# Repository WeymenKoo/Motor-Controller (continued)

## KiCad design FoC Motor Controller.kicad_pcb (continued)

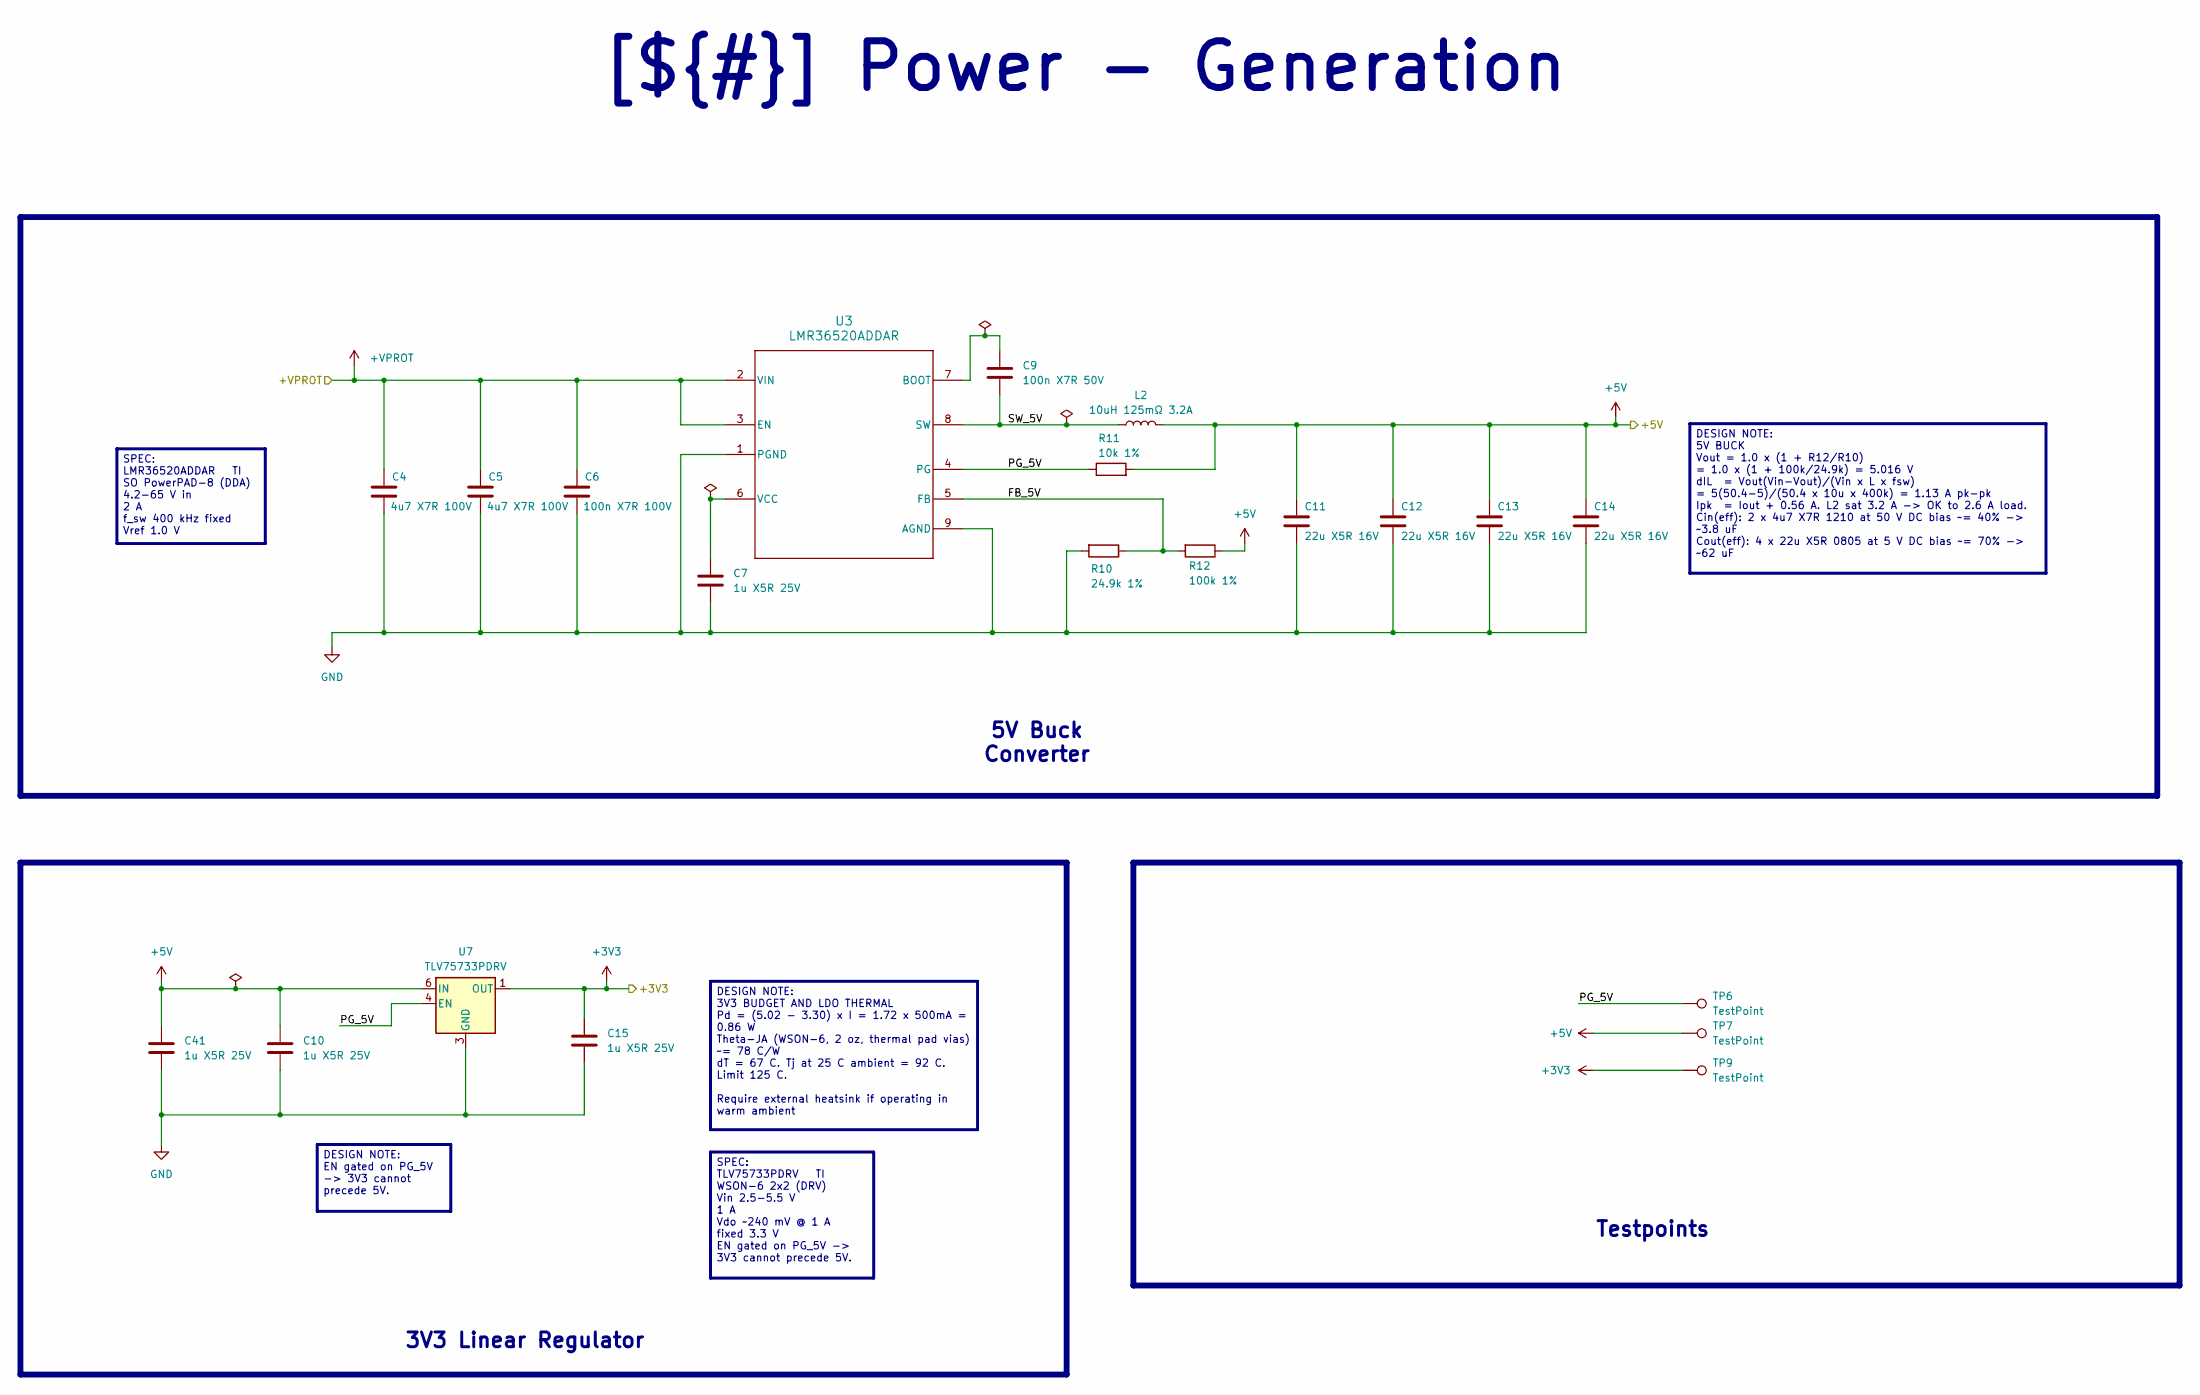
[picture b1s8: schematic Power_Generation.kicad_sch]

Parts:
C4, C5: 4u7 X7R 100V; C_1210_3225Metric_Pad1.33x2.70mm_HandSolder
C6: 100n X7R 100V; C_0603_1608Metric_Pad1.08x0.95mm_HandSolder
C7, C10, C15, C41: 1u X5R 25V; C_0603_1608Metric
C9: 100n X7R 50V; C_0402_1005Metric
C11, C12, C13, C14: 22u X5R 16V; C_0805_2012Metric
L2: 10uH 125mΩ 3.2A; L_Changjiang_FXL0530
R10: 24.9k 1%; R_0402_1005Metric
R11: 10k 1%; R_0402_1005Metric
R12: 100k 1%; R_0402_1005Metric
TP6, TP7, TP9: TestPoint; TestPoint-0.5mm
U3: LMR36520ADDAR; DDA0008J
U7: TLV75733PDRV; WDFN-6_2x2mm

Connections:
+3V3: C15.1, TP9.1 (1_1), U7.1 (OUT); also elsewhere on the board
+5V: C10.1, C11.1, C12.1, C13.1, C14.1, C41.1, L2.2, R11.2, R12.1, TP7.1 (1_1), U7.6 (IN); also elsewhere on the board
+VPROT: C4.1, C5.1, C6.1, U3.2 (VIN), U3.3 (EN); also elsewhere on the board
/Project Architecture/Power - Generation/FB_5V: R10.1, R12.2, U3.5 (FB)
/Project Architecture/Power - Generation/PG_5V: R11.1, TP6.1 (1_1), U3.4 (PG), U7.4 (EN)
/Project Architecture/Power - Generation/SW_5V: C9.2, L2.1, U3.8 (SW)
GND: C4.2, C5.2, C6.2, C7.2, C10.2, C11.2, C12.2, C13.2, C14.2, C15.2, C41.2, R10.2, U3.1 (PGND), U3.9 (AGND), U7.3 (GND), U7.7 (GND); also elsewhere on the board
unnamed: C9.1, U3.7 (BOOT)
unnamed: C7.1, U3.6 (VCC)

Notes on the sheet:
3V3 Linear Regulator
Testpoints
SPEC: TLV75733PDRV TI WSON-6 2x2 (DRV) Vin 2.5-5.5 V 1 A Vdo ~240 mV @ 1 A fixed 3.3 V EN gated on PG_5V -> 3V3 cannot precede 5V.
DESIGN NOTE: EN gated on PG_5V -> 3V3 cannot precede 5V.
DESIGN NOTE: 5V BUCK Vout = 1.0 x (1 + R12/R10) = 1.0 x (1 + 100k/24.9k) = 5.016 V dIL = Vout(Vin-Vout)/(Vin x L x fsw) = 5(50.4-5)/(50.4 x 10u x 400k) = 1.13 A pk-pk Ipk = Iout + 0.56 A. L2 sat 3.2 A -> OK to 2.6 A load. Cin(eff): 2 x 4u7 X7R 1210 at 50 V DC bias ~= 40% -> ~3.8 uF Cout(eff): 4 x 2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
DESIGN NOTE: 3V3 BUDGET AND LDO THERMAL Pd = (5.02 - 3.30) x I = 1.72 x 500mA = 0.86 W Theta-JA (WSON-6, 2 oz, thermal pad vias) ~= 78 C/W dT = 67 C. Tj at 25 C ambient = 92 C. Limit 125 C. Require external heatsink if operating in warm ambient
5V Buck Converter
[${#}] Power - Generation
SPEC: LMR36520ADDAR TI SO PowerPAD-8 (DDA) 4.2-65 V in 2 A f_sw 400 kHz fixed Vref 1.0 V

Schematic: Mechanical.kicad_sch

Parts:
C73, C74, C75, C76: 1n X7R 1kV; C_0603_1608Metric_Pad1.08x0.95mm_HandSolder
H4, H5, H6, H7: M3_MountingHole_Pad; MountingHole_3.2mm_M3_Pad_Via
R56, R57, R59: 0R 1% 1/8W; R_0805_2012Metric; not fitted
R58: 0R 1% 1/8W; R_0805_2012Metric

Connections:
CHASSIS1: C73.1, H4.1 (1_1), R56.1
CHASSIS2: C74.1, H5.1 (1_1), R57.1
CHASSIS3: C75.1, H6.1 (1_1), R58.1; also elsewhere on the board
CHASSIS4: C76.1, H7.1 (1_1), R59.1
GND: C73.2, C74.2, C75.2, C76.2, R56.2, R57.2, R58.2, R59.2; also elsewhere on the board

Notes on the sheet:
[${#}] Mechanical - Mounting Holes
DESIGN NOTE: 0-Ohmresistor provides low-impedance bond between chassis and signal GND. Be aware of ground loops through cable shield.
DESIGN NOTE: Optional RC filter for chassis grounding. Capacitors offer multi-point low-impedance connections at high-frequencies.

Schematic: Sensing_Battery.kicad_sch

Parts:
C60: 100n X7R 50V; C_0402_1005Metric
R36: 2k 1%; R_0402_1005Metric
R72: 24.9k 1%; R_0402_1005Metric
R73: 12.4k 1%; R_0402_1005Metric

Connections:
+VPROT: R72.1; also elsewhere on the board
/Project Architecture/MCU - IOs/VBAT_SENSE: C60.1, R36.1, R73.2; also elsewhere on the board
GND: C60.2, R36.2; also elsewhere on the board
unnamed: R72.2, R73.1

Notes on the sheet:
Battery Voltage Sensor
[${#}] Sensing - Battery
DESIGN NOTE: Ratio = R36/(R72+R73+R36) = 2/(24.9+12.4+2) = 2/39.3 = 0.05089 at 50.4 V -> 2.565 V at 56.0 V -> 2.850 V clips at VREF+ = 3.3 V when Vbus = 64.8 V Divider current at 50.4 V = 1.283 mA (continuous pack drain) P(R72) = 41 mW, P(R73) = 20 mW Rth = (R72+R73) || R36 = 1.90 k tau = 190 us, f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

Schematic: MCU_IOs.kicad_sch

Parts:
C16: 22u X5R 16V; C_0805_2012Metric
C17, C20, C24: 1u X5R 25V; C_0603_1608Metric
C18, C19, C21, C22, C23: 100n X7R 50V; C_0402_1005Metric
C25, C26, C27: 2n2 X7R 50V; C_0402_1005Metric
C28, C29: 12pF 50V C0G; C_0402_1005Metric
R13, R14, R15: 56R 1%; R_0402_1005Metric
TP11, TP12, TP13, TP14, TP15, TP16, TP17, TP18, TP19, TP20, TP21, TP22, TP23, TP24, TP25, TP26, TP27, TP28, TP29, TP30, TP31, TP32, TP33, TP34, TP35, TP36: TestPoint; TestPoint-0.5mm
U5: STM32G431RBTx; LQFP-64_10x10mm_P0.5mm
X1: SMD3225-4; Crystal_SMD_3225-4Pin_3.2x2.5mm

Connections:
+3V3: C16.1, C17.1, C18.1, C19.1, C20.1, C21.1, C22.1, C23.1, C24.1, U5.1 (VBAT), U5.16 (VDD), U5.28 (VREF+), U5.29 (VDDA), U5.32 (VDD), U5.48 (VDD), U5.64 (VDD); also elsewhere on the board
/Project Architecture/Interface - CAN FD/FDCAN_RX: TP12.1 (1_1), U5.61 (PB8); also elsewhere on the board
/Project Architecture/Interface - CAN FD/FDCAN_TX: TP11.1 (1_1), U5.62 (PB9); also elsewhere on the board
/Project Architecture/Interface - Interconnects/I2C3_SCL: U5.40 (PC8); also elsewhere on the board
/Project Architecture/Interface - Interconnects/I2C3_SDA: U5.41 (PC9); also elsewhere on the board
/Project Architecture/Interface - Interconnects/NRST: U5.7 (PG10); also elsewhere on the board
/Project Architecture/Interface - Interconnects/POS_SENSOR_CLK: U5.19 (PA5); also elsewhere on the board
/Project Architecture/Interface - Interconnects/POS_SENSOR_CS: U5.18 (PA4); also elsewhere on the board
/Project Architecture/Interface - Interconnects/POS_SENSOR_CS2: U5.22 (PC4); also elsewhere on the board
/Project Architecture/Interface - Interconnects/POS_SENSOR_MISO: U5.20 (PA6); also elsewhere on the board
/Project Architecture/Interface - Interconnects/POS_SENSOR_MOSI: U5.21 (PA7); also elsewhere on the board
/Project Architecture/Interface - Interconnects/SWCLK: U5.50 (PA14); also elsewhere on the board
/Project Architecture/Interface - Interconnects/SWDIO: U5.49 (PA13); also elsewhere on the board
/Project Architecture/Interface - Interconnects/UART1_RX: TP14.1 (1_1), U5.59 (PB6); also elsewhere on the board
/Project Architecture/Interface - Interconnects/UART1_TX: TP13.1 (1_1), U5.60 (PB7); also elsewhere on the board
/Project Architecture/MCU - IOs/DRV_CAL: TP29.1 (1_1), U5.38 (PC6); also elsewhere on the board
/Project Architecture/MCU - IOs/DRV_CS: TP33.1 (1_1), U5.55 (PD2); also elsewhere on the board
/Project Architecture/MCU - IOs/DRV_ENABLE: TP28.1 (1_1), U5.39 (PC7); also elsewhere on the board
/Project Architecture/MCU - IOs/DRV_MISO: TP30.1 (1_1), U5.53 (PC11); also elsewhere on the board
/Project Architecture/MCU - IOs/DRV_MOSI: TP31.1 (1_1), U5.54 (PC12); also elsewhere on the board
/Project Architecture/MCU - IOs/DRV_SCLK: TP32.1 (1_1), U5.52 (PC10); also elsewhere on the board
/Project Architecture/MCU - IOs/DRV_nFAULT: TP27.1 (1_1), U5.51 (PA15); also elsewhere on the board
/Project Architecture/MCU - IOs/FILTER_SOA: C27.1, R15.1, TP17.1 (1_1), U5.33 (PB11)
/Project Architecture/MCU - IOs/FILTER_SOB: C26.1, R14.1, TP16.1 (1_1), U5.34 (PB12)
/Project Architecture/MCU - IOs/FILTER_SOC: C25.1, R13.1, TP15.1 (1_1), U5.36 (PB14)
/Project Architecture/MCU - IOs/MCU_LED: U5.58 (PB5); also elsewhere on the board
/Project Architecture/MCU - IOs/MOT_TEMP_SENSE: TP36.1 (1_1), U5.26 (PB2); also elsewhere on the board
/Project Architecture/MCU - IOs/OSC_IN: C29.1, U5.5 (PF0), X1.1
/Project Architecture/MCU - IOs/OSC_OUT: C28.1, U5.6 (PF1), X1.3
/Project Architecture/MCU - IOs/PA0: U5.12 (PA0)
/Project Architecture/MCU - IOs/PA1: U5.13 (PA1)
/Project Architecture/MCU - IOs/PA2: U5.14 (PA2)
/Project Architecture/MCU - IOs/PA3: U5.17 (PA3)
/Project Architecture/MCU - IOs/PB3: U5.56 (PB3)
/Project Architecture/MCU - IOs/PB10: U5.30 (PB10)
/Project Architecture/MCU - IOs/PB13: U5.35 (PB13)
/Project Architecture/MCU - IOs/PC0: U5.8 (PC0)
/Project Architecture/MCU - IOs/PC1: U5.9 (PC1)
/Project Architecture/MCU - IOs/PC2: U5.10 (PC2)
/Project Architecture/MCU - IOs/PC3: U5.11 (PC3); also elsewhere on the board
/Project Architecture/MCU - IOs/PC5: U5.23 (PC5)
/Project Architecture/MCU - IOs/PC13: U5.2 (PC13)
/Project Architecture/MCU - IOs/PC14: U5.3 (PC14)
/Project Architecture/MCU - IOs/PC15: U5.4 (PC15)
/Project Architecture/MCU - IOs/PWM_PHASEA_H: TP21.1 (1_1), U5.42 (PA8); also elsewhere on the board
/Project Architecture/MCU - IOs/PWM_PHASEA_L: TP22.1 (1_1), U5.45 (PA11); also elsewhere on the board
/Project Architecture/MCU - IOs/PWM_PHASEB_H: TP23.1 (1_1), U5.43 (PA9); also elsewhere on the board
/Project Architecture/MCU - IOs/PWM_PHASEB_L: TP24.1 (1_1), U5.46 (PA12); also elsewhere on the board
/Project Architecture/MCU - IOs/PWM_PHASEC_H: TP25.1 (1_1), U5.44 (PA10); also elsewhere on the board
/Project Architecture/MCU - IOs/PWM_PHASEC_L: TP26.1 (1_1), U5.37 (PB15); also elsewhere on the board
/Project Architecture/MCU - IOs/PWR_LED: U5.57 (PB4); also elsewhere on the board
/Project Architecture/MCU - IOs/SOA: R15.2, TP20.1 (1_1); also elsewhere on the board
/Project Architecture/MCU - IOs/SOB: R14.2, TP19.1 (1_1); also elsewhere on the board
/Project Architecture/MCU - IOs/SOC: R13.2, TP18.1 (1_1); also elsewhere on the board
/Project Architecture/MCU - IOs/TEMP_SENSE: TP35.1 (1_1), U5.25 (PB1); also elsewhere on the board
/Project Architecture/MCU - IOs/VBAT_SENSE: TP34.1 (1_1), U5.24 (PB0); also elsewhere on the board
GND: C16.2, C17.2, C18.2, C19.2, C20.2, C21.2, C22.2, C23.2, C24.2, C25.2, C26.2, C27.2, C28.2, C29.2, U5.15 (VSS), U5.27 (VSSA), U5.31 (VSS), U5.47 (VSS), U5.63 (VSS), X1.2, X1.4; also elsewhere on the board

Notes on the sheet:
SWD
DESIGN NOTE: CALC - CRYSTAL LOAD CL = (C28 x C29)/(C28 + C29) + Cstray = (12 x 12)/24 + ~5 = 11 pF Selected a crystal specified for CL = 11-12 pF.
Analog IO
REVIEW
[${#}] MCU - IOs
SPEC: ADC CHANNEL MAP FILTER_SOA PB11 ADC1_IN14 / ADC2_IN14 (both) FILTER_SOB PB12 ADC1_IN11 (ADC1 only) FILTER_SOC PB14 ADC1_IN5 (ADC1 only) VBAT_SENSE PB0 ADC1_IN15 TEMP_SENSE PB1 ADC1_IN12 MOT_TEMP PB2 ADC2_IN12 Simultaneous dual-ADC sampling MUST pair SOA (on ADC2) with SOB or SOC (on ADC1). Ph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
MCU - STM32G431RBT6
FIRMWARE - MANDATORY AT BOOT 1. Program nSWBOOT0 = 0 so BOOT0 comes from the option bit, not PB8 (PB8 = FDCAN1_RX). 2. Set PWR_CR3.UCPD1_DBDIS = 1 BEFORE enabling TIM1. PA9/PA10 (PWM_PHASEB_H / PWM_PHASEC_H) are UCPD1_DBCC1/2. A high level enables internal 5.1k pull-downs on PB6 (UART TX) and PB4 (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
Testpoints
Digital IO

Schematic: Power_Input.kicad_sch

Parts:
D1: SMCJ51CA; D_SMC_TVS
H8, H9: Power; MountingHole_3.2mm_M3_Pad_Via

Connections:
+VPROT: D1.2 (A), H8.1 (1_1); also elsewhere on the board
GND: D1.1 (K), H9.1 (1_1); also elsewhere on the board

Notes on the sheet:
ACCEPTED RISK: D1 clamps at 82.4 V. Downstream absolute maximums: DRV8323 VM/VDRAIN 65 V LMR36520 VIN 65 V TLV75733 VIN 5.5 V (fed from +5V, not exposed) D1 therefore does NOT protect the board against an event large enough to engage it. SOLUTION: Upstream PDB handles protection
ASSEMBLY: D3.2mm solder pad, no connector
SPEC: SMCJ51CA Littelfuse SMC / DO-214AB Vrwm 51 V Vbr(min) 56.7 V Vclamp 82.4 V @ 18.2 A 1500 W Bidirectional (CA suffix)
Input Power
[${#}] Power - Input

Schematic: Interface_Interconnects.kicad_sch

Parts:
C42: 2n2 X7R 50V; C_0402_1005Metric
C67, C70, C72, C78, C81: 100n X7R 50V; C_0402_1005Metric
C68: 47n X7R 100V; C_0603_1608Metric_Pad1.08x0.95mm_HandSolder
D4, D7: PESD2CANFD24V-K; TVS_PESD2CANFD24V-UX; PARTREV V.4
J1, J3, J4, J5: Conn_01x04_MountingPin; JST_GH_BM04B-GHS-TBT_1x04-1MP_P1.25mm_Vertical
J2: Conn_01x03; 1x03_P2.54mm; not fitted
J6: Conn_01x07_MountingPin; JST_GH_BM07B-GHS-TBT_1x07-1MP_P1.25mm_Vertical
J7: Conn_01x05; PinHeader_1x05_P2.54mm_Vertical
J10, J11: Conn_01x02_MountingPin; JST_GH_BM02B-GHS-TBT_1x02-1MP_P1.25mm_Vertical
R41: 1k 1%; R_0402_1005Metric
R42, R44: 2k 1%; R_0402_1005Metric
R45, R46: 60R4 1%; R_0805_2012Metric
R47, R48, R49, R50, R51, R52, R53, R54: 100R 1%; R_0402_1005Metric
SW1: SW_Push_DPDT; Slide_DPDT_SMD_7.2x3.5mm

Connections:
+3V3: C72.1, C78.1, C81.1, J1.2, J3.2, J6.2, J7.1, R42.1, R44.1; also elsewhere on the board
+5V: C70.1, J6.1; also elsewhere on the board
/Project Architecture/Interface - CAN FD/FDCAN_N: D4.2, D7.2, J2.1, J4.2, J5.2, SW1.4 (A); also elsewhere on the board
/Project Architecture/Interface - CAN FD/FDCAN_P: D4.1, D7.1, J2.2, J4.3, J5.3, SW1.1 (A); also elsewhere on the board
/Project Architecture/Interface - Interconnects/AUX2_A: J6.4, R47.1
/Project Architecture/Interface - Interconnects/AUX2_B: J6.5, R49.1
/Project Architecture/Interface - Interconnects/AUX2_C: J6.6, R51.1
/Project Architecture/Interface - Interconnects/AUX2_D: J6.7, R53.1
/Project Architecture/Interface - Interconnects/FDCAN_TERM_B: R46.2, SW1.5 (B)
/Project Architecture/Interface - Interconnects/FDCAN_TERM_MID: C68.1, R45.2, R46.1
/Project Architecture/Interface - Interconnects/FDCAN_TERM_T: R45.1, SW1.2 (B)
/Project Architecture/Interface - Interconnects/I2C3_SCL: R44.2, R50.2; also elsewhere on the board
/Project Architecture/Interface - Interconnects/I2C3_SDA: R42.2, R48.2; also elsewhere on the board
/Project Architecture/Interface - Interconnects/MOT_NTC_H: J10.1; also elsewhere on the board
/Project Architecture/Interface - Interconnects/MOT_NTC_L: J10.2; also elsewhere on the board
/Project Architecture/Interface - Interconnects/NRST: C67.1, J7.2; also elsewhere on the board
/Project Architecture/Interface - Interconnects/POS_SENSOR_CLK: R49.2; also elsewhere on the board
/Project Architecture/Interface - Interconnects/POS_SENSOR_CS2: R47.2; also elsewhere on the board
/Project Architecture/Interface - Interconnects/POS_SENSOR_MISO: R51.2; also elsewhere on the board
/Project Architecture/Interface - Interconnects/POS_SENSOR_MOSI: R53.2; also elsewhere on the board
/Project Architecture/Interface - Interconnects/SWCLK: J7.3; also elsewhere on the board
/Project Architecture/Interface - Interconnects/SWDIO: J7.4; also elsewhere on the board
/Project Architecture/Interface - Interconnects/UART1_RX: R54.2; also elsewhere on the board
/Project Architecture/Interface - Interconnects/UART1_TX: R52.2; also elsewhere on the board
/Project Architecture/MCU - IOs/DRV_ENABLE: C42.1, J11.1, R41.1; also elsewhere on the board
/Project Architecture/MCU - IOs/PC3: R41.2; also elsewhere on the board
CHASSIS3: D4.3, D7.3; also elsewhere on the board
GND: C42.2, C67.2, C68.2, C70.2, C72.2, C78.2, C81.2, J1.1, J2.3, J3.1, J4.4, J5.4, J6.3, J7.5, J11.2; also elsewhere on the board
unnamed: J1.3, R52.1
unnamed: J1.4, R54.1
unnamed: J3.3, R48.1
unnamed: J3.4, R50.1

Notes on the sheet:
DESIGN NOTE: Loop closed = PC3 low = run; Loop open OR cable unplugged = PC3 high = hardware break.
DESIGN NOTE: J6 shares SPI1 (SCK/MISO/MOSI) with the on-board AS5047P (U1). Isolation is by chip select only: U1 on PA4, remote on PC4. AS5047P tri-states MISO when CSn is high (datasheet t_OZ), so two slaves on one bus is valid - but firmware MUST NOT assert both chip selects.
SWD (2.54mm Pin Header)
AUX2 Connector (Position Sensor SPI)
DESIGN NOTE: No ESD protection for prototype. Expected to be in lab environment.
Temperature
DESIGN NOTE: UART PIN NAMING Net UART1_TX lands on PB7 = USART1_RX. Net UART1_RX lands on PB6 = USART1_TX.
[${#}] Interface - Interconnects
FD_CAN Connectors and Termination

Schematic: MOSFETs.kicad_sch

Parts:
C34, C37, C39: 100uF 100V; CP_Radial_D10.0mm_P5.00mm; Voltage 1kV; Tolerance 100%
C35, C36, C45, C46, C56, C57: 2n2 X7R 100V; C_0805_2012Metric; not fitted
C38, C49, C58: 100n X7R 100V; C_0603_1608Metric_Pad1.08x0.95mm_HandSolder
C40, C43, C44, C47, C48, C50, C51, C52, C59: 4u7 X7R 100V; C_1210_3225Metric_Pad1.33x2.70mm_HandSolder
H1, H2, H3: Phase; MountingHole_3.2mm_M3_Pad_Via
NT1, NT2, NT3, NT4, NT5, NT6, NT7, NT8, NT9: NetTie_2; NetTie-2_SMD_Pad0.5mm
Q3, Q4, Q5, Q6, Q7, Q8: ISC030N10NM6; IFX-PG-TDSON-8-36-V
R20, R21, R25, R26, R30, R31: 0R 1% 1/8W; R_0805_2012Metric_Pad1.20x1.40mm_HandSolder
R22, R27, R32: 3mΩ 3W 1%; R_2512_6332Metric_Pad1.40x3.35mm_HandSolder
R23, R24, R28, R29, R33, R34: 3R9 1% 1/8W; R_0805_2012Metric_Pad1.20x1.40mm_HandSolder; not fitted

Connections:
+VPROT: C34.1, C37.1, C38.1, C39.1, C40.1, C43.1, C44.1, C47.1, C48.1, C49.1, C50.1, C51.1, C52.1, C58.1, C59.1, Q3.5 (DRAIN), Q3.6 (DRAIN), Q3.7 (DRAIN), Q3.8 (DRAIN), Q5.5 (DRAIN), Q5.6 (DRAIN), Q5.7 (DRAIN), Q5.8 (DRAIN), Q7.5 (DRAIN), Q7.6 (DRAIN), Q7.7 (DRAIN), Q7.8 (DRAIN), R23.1, R28.1, R33.1; also elsewhere on the board
/Project Architecture/Motor Control - Driver/GHA: R20.2; also elsewhere on the board
/Project Architecture/Motor Control - Driver/GHB: R25.2; also elsewhere on the board
/Project Architecture/Motor Control - Driver/GHC: R30.2; also elsewhere on the board
/Project Architecture/Motor Control - Driver/GLA: R21.2; also elsewhere on the board
/Project Architecture/Motor Control - Driver/GLB: R26.2; also elsewhere on the board
/Project Architecture/Motor Control - Driver/GLC: R31.2; also elsewhere on the board
/Project Architecture/Motor Control - Driver/MOSFETs/GH_A: Q3.4 (GATE), R20.1
/Project Architecture/Motor Control - Driver/MOSFETs/GH_B: Q5.4 (GATE), R25.1
/Project Architecture/Motor Control - Driver/MOSFETs/GH_C: Q7.4 (GATE), R30.1
/Project Architecture/Motor Control - Driver/MOSFETs/GL_A: Q4.4 (GATE), R21.1
/Project Architecture/Motor Control - Driver/MOSFETs/GL_B: Q6.4 (GATE), R26.1
/Project Architecture/Motor Control - Driver/MOSFETs/GL_C: Q8.4 (GATE), R31.1
/Project Architecture/Motor Control - Driver/MOSFETs/OUT_A: C35.2, C36.1, H1.1 (1_1), NT3.2, Q3.1 (SOURCE), Q3.2 (SOURCE), Q3.3 (SOURCE), Q4.5 (DRAIN), Q4.6 (DRAIN), Q4.7 (DRAIN), Q4.8 (DRAIN)
/Project Architecture/Motor Control - Driver/MOSFETs/OUT_B: C45.2, C46.1, H2.1 (1_1), NT6.2, Q5.1 (SOURCE), Q5.2 (SOURCE), Q5.3 (SOURCE), Q6.5 (DRAIN), Q6.6 (DRAIN), Q6.7 (DRAIN), Q6.8 (DRAIN)
/Project Architecture/Motor Control - Driver/MOSFETs/OUT_C: C56.2, C57.1, H3.1 (1_1), NT9.2, Q7.1 (SOURCE), Q7.2 (SOURCE), Q7.3 (SOURCE), Q8.5 (DRAIN), Q8.6 (DRAIN), Q8.7 (DRAIN), Q8.8 (DRAIN)
/Project Architecture/Motor Control - Driver/MOSFETs/RSHUNT_N_A: NT2.1; also elsewhere on the board
/Project Architecture/Motor Control - Driver/MOSFETs/RSHUNT_N_B: NT5.1; also elsewhere on the board
/Project Architecture/Motor Control - Driver/MOSFETs/RSHUNT_N_C: NT8.1; also elsewhere on the board
/Project Architecture/Motor Control - Driver/MOSFETs/RSHUNT_P_A: NT1.1; also elsewhere on the board
/Project Architecture/Motor Control - Driver/MOSFETs/RSHUNT_P_B: NT4.1; also elsewhere on the board
/Project Architecture/Motor Control - Driver/MOSFETs/RSHUNT_P_C: NT7.1; also elsewhere on the board
/Project Architecture/Motor Control - Driver/MOSFETs/SOURCE_A: C38.2, NT1.2, Q4.1 (SOURCE), Q4.2 (SOURCE), Q4.3 (SOURCE), R22.1, R24.2
/Project Architecture/Motor Control - Driver/MOSFETs/SOURCE_B: C49.2, NT4.2, Q6.1 (SOURCE), Q6.2 (SOURCE), Q6.3 (SOURCE), R27.1, R29.2
/Project Architecture/Motor Control - Driver/MOSFETs/SOURCE_C: C58.2, NT7.2, Q8.1 (SOURCE), Q8.2 (SOURCE), Q8.3 (SOURCE), R32.1, R34.2
/Project Architecture/Motor Control - Driver/SHA: NT3.1; also elsewhere on the board
/Project Architecture/Motor Control - Driver/SHB: NT6.1; also elsewhere on the board
/Project Architecture/Motor Control - Driver/SHC: NT9.1; also elsewhere on the board
GND: C34.2, C37.2, C39.2, C40.2, C43.2, C44.2, C47.2, C48.2, C50.2, C51.2, C52.2, C59.2, NT2.2, NT5.2, NT8.2, R22.2, R27.2, R32.2; also elsewhere on the board
unnamed: C35.1, R23.2
unnamed: C36.2, R24.1
unnamed: C45.1, R28.2
unnamed: C46.2, R29.1
unnamed: C56.1, R33.2
unnamed: C57.2, R34.1

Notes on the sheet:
[${#}] MOSFETs
SPEC: Q3-Q8 ISC030N10NM6 Infineon TOLL (PG-HSOF-8) 100 V 3.0 mR typ @ 10 V Qg [FILL] nC Qgd [FILL] nC
DESIGN NOTE: CALC - DC LINK Bulk 3 x 100 uF = 300 uF (polymer, negligible DC derating) MLCC 9 x 4u7 = 42.3 uF nominal at 50 V DC bias, 1210 X7R ~= 0.4 -> 16.9 uF effective Bus ripple dV ~= Idc/(fsw x C) = [FILL]/( [FILL] x 316u) = [FILL] V Ripple current requirement: [FILL] A RMS vs 3 x [FILL] A ra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
REVIEW
DESIGN NOTE: CALC - CONDUCTION LOSS Rds(on) at Tj 125 C ~= 3.0 mR x 1.5 = 4.5 mR P_cond = 3 x Iph_rms^2 x Rds(on) = 3 x [FILL]^2 x 4.5 mR = [FILL] W Shunt P = Iph_rms^2 x 3 mR = [FILL] W each (3 W rated) Vsense at 20 A = 60 mV
DESIGN NOTE: CALC - CURRENT SENSE Rshunt = 3 mR, bidirectional, VREF = 3.3 V, zero at 1.65 V Gain 5 -> +/-110 A Gain 20 -> +/-27.5 A Gain 10 -> +/-55 A Gain 40 -> +/-13.75 A SELECTED: gain 20 V/V ADC resolution at gain 20: (3.3/4096) / 20 / 3 mR = 13.4 mA per LSB Vsense at 20 A = 60 mV (within +/-1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

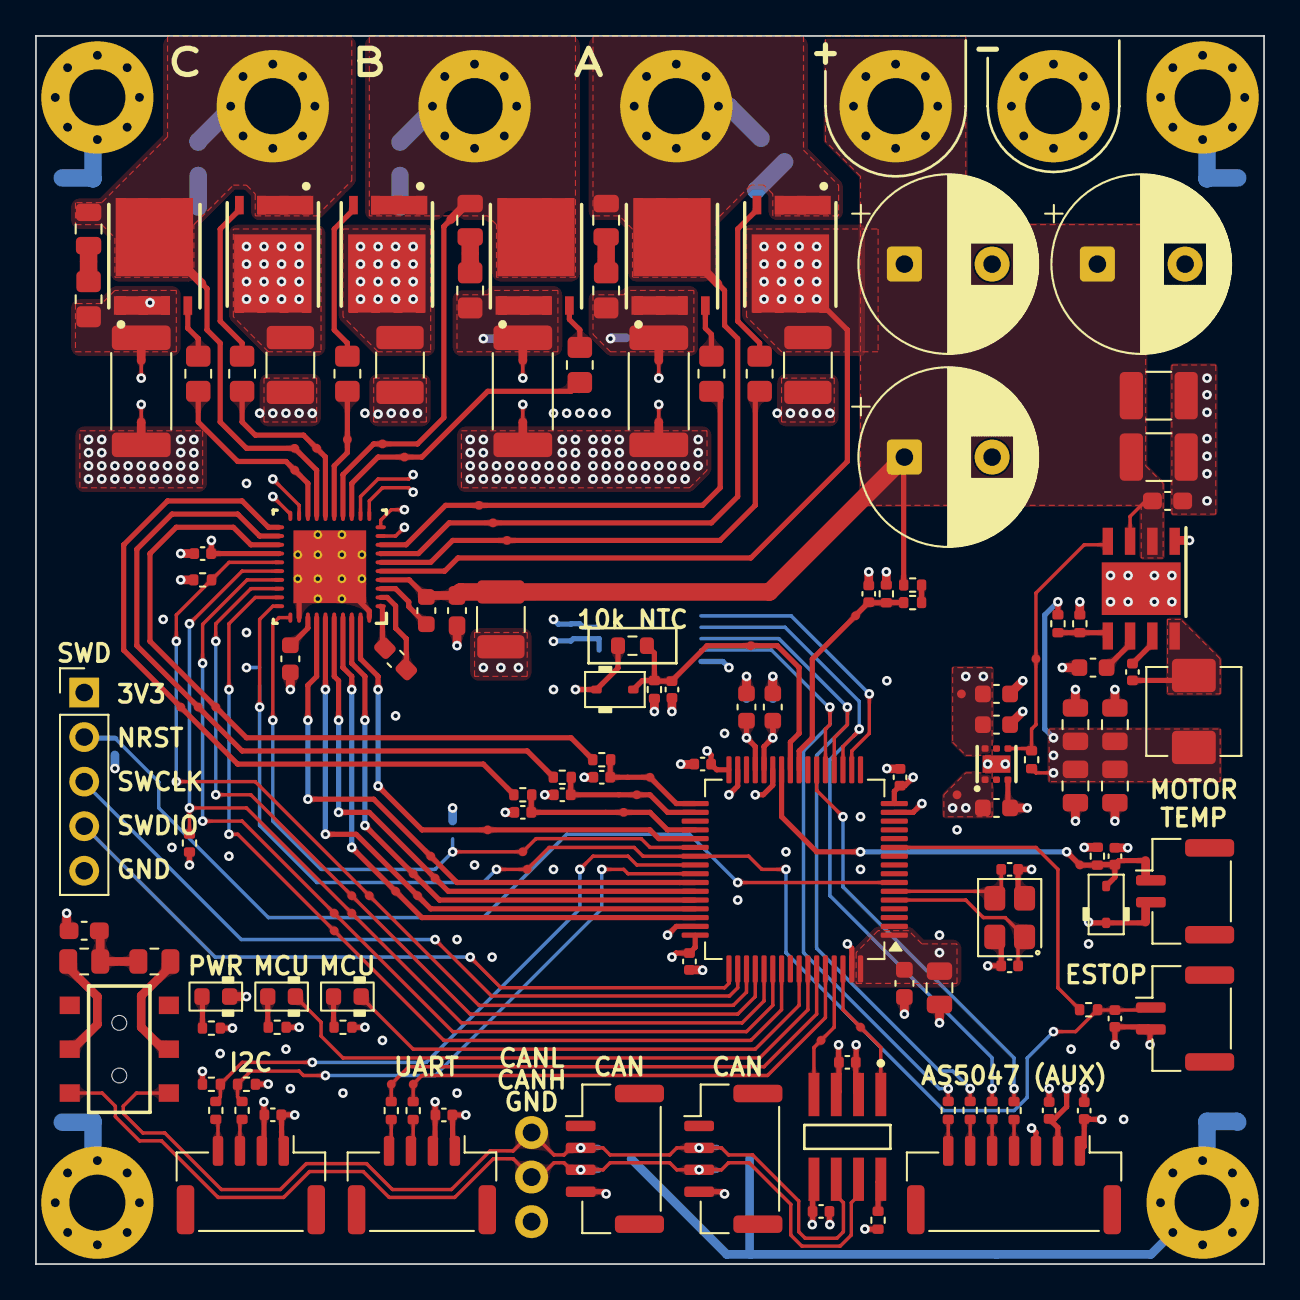
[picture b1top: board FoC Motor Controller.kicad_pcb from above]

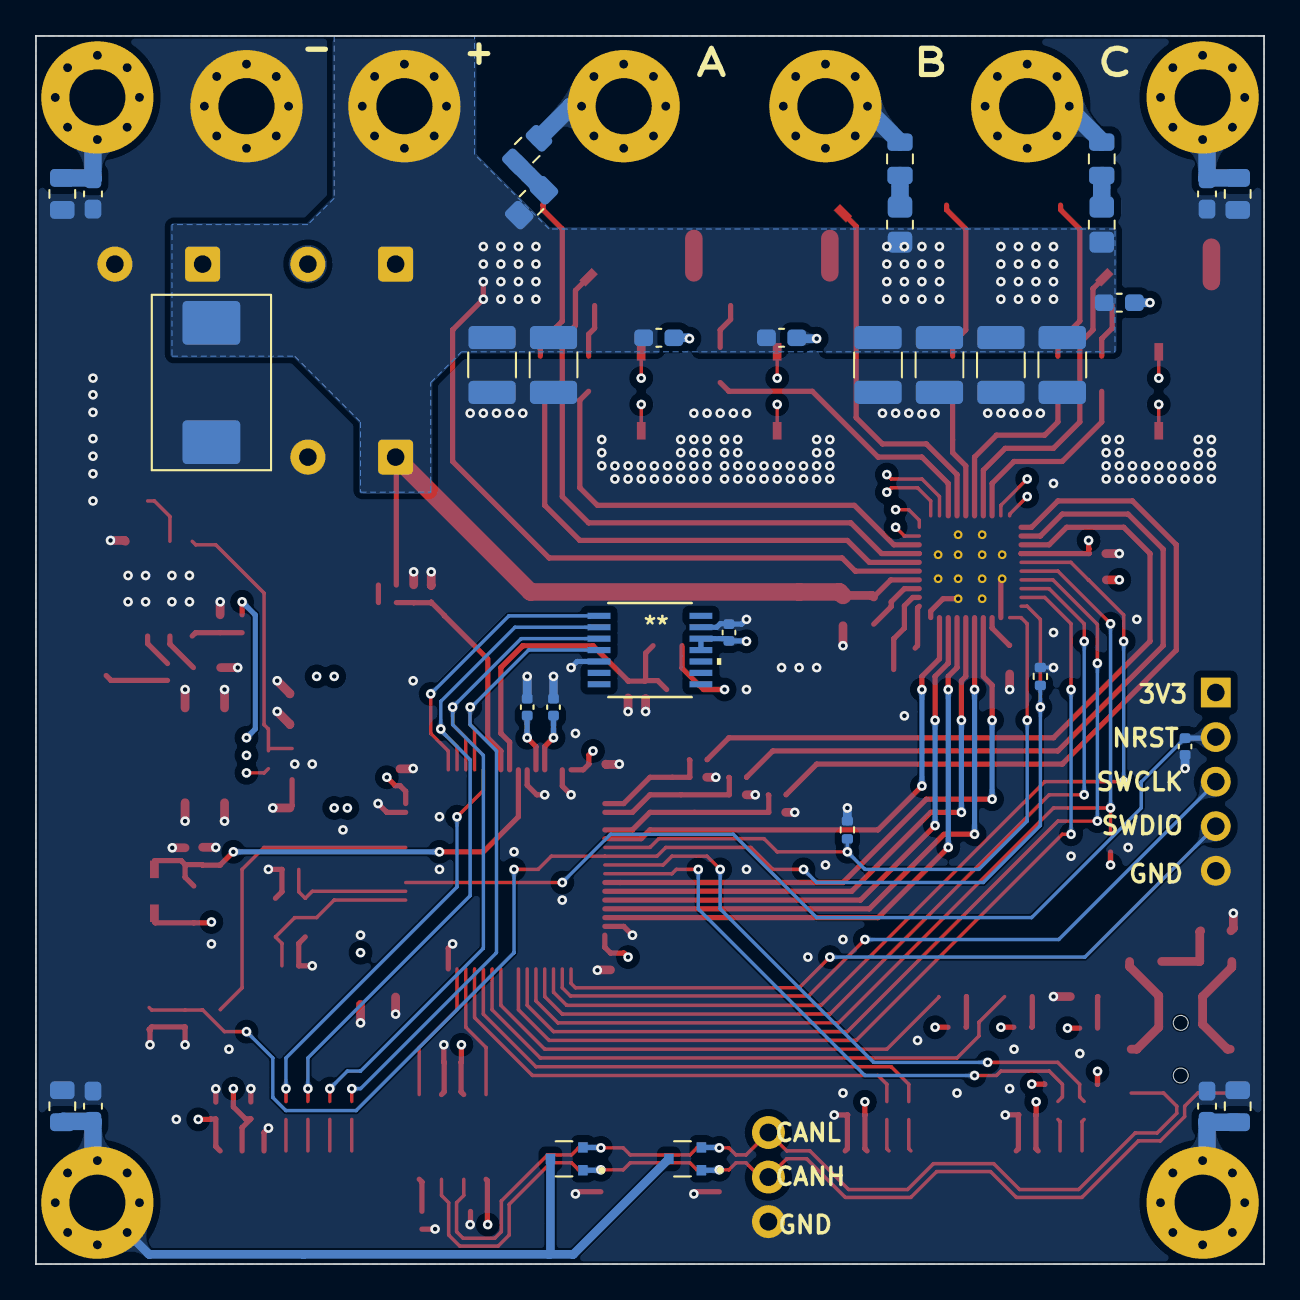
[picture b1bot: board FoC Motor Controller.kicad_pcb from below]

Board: 6 copper layers, 70.0 x 70.0 mm, 212 parts (33 on the bottom side), 111 nets.

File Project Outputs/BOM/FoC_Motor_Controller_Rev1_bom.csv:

"Reference","Value","Datasheet","Footprint","Qty","Description"
"C4,C5,C40,C43,C44,C47,C48,C50,C51,C52,C59,C80","4u7 X7R 100V","","Capacitor_SMD:C_1210_3225Metric_Pad1.33x2.70mm_HandSolder","12","Unpolarized capacitor"
"C6,C33,C38,C49,C58","100n X7R 100V","","Capacitor_SMD:C_0603_1608Metric_Pad1.08x0.95mm_HandSolder","5","Unpolarized capacitor"
"C7,C10,C15,C17,C20,C24,C31,C41,C79","1u X5R 25V","","Capacitor_SMD:C_0603_1608Metric","9","Unpolarized capacitor"
"C9,C18,C19,C21,C22,C23,C32,C60,C61,C62,C65,C66,C67,C70,C72,C77,C78,C81","100n X7R 50V","","Capacitor_SMD:C_0402_1005Metric","18","Unpolarized capacitor"
"C11,C12,C13,C14,C16","22u X5R 16V","","Capacitor_SMD:C_0805_2012Metric","5","Unpolarized capacitor"
"C25,C26,C27,C42","2n2 X7R 50V","","Capacitor_SMD:C_0402_1005Metric","4","Unpolarized capacitor"
"C28,C29","12pF 50V C0G","","Capacitor_SMD:C_0402_1005Metric","2","Unpolarized capacitor"
"C30,C68","47n X7R 100V","","Capacitor_SMD:C_0603_1608Metric_Pad1.08x0.95mm_HandSolder","2","Unpolarized capacitor"
"C34,C37,C39","100uF 100V","https://cdn.sparkfun.com/assets/8/a/4/a/5/Kemet_Capacitor_Da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","Capacitor_THT:CP_Radial_D10.0mm_P5.00mm","3","Polarized capacitor, US symbol"
"C73,C74,C75,C76","1n X7R 1kV","","Capacitor_SMD:C_0603_1608Metric_Pad1.08x0.95mm_HandSolder","4","Unpolarized capacitor"
"D1","SMCJ51CA","https://www.tme.eu/Document/535c4da69331b5e4fe2b7f8cdcd9eb69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","PCM_Diode_SMD_AKL:D_SMC_TVS","1","SMC Bidirectional TVS Diode, 51V, 1500W, Alternate KiCAD Library"
"D4,D7","PESD2CANFD24V-K","","PESD2CANFD24V-UX:TVS_PESD2CANFD24V-UX","2","ESD Suppressor Diode TVS Bi-Dir 24V 42Vc Automotive 3-Pin SC-70 T/R"
"DZ2,DZ3","MM3Z3V3ST","https://www.tme.eu/Document/59602a643d19bb5d35c4e4c7d37742b4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","PCM_Diode_SMD_AKL:D_SOD-323","2","SOD-323 Zener diode, 3.3V, 300mW, Alternate KiCAD Library"
"J1,J3,J4,J5","Conn_01x04_MountingPin","","Connector_JST:JST_GH_BM04B-GHS-TBT_1x04-1MP_P1.25mm_Vertical","4","Generic connectable mounting pin connector, single row, 01x04, script generated (kicad-library-utils/schlib/autogen/connector/)"
"J6","Conn_01x07_MountingPin","","Connector_JST:JST_GH_BM07B-GHS-TBT_1x07-1MP_P1.25mm_Vertical","1","Generic connectable mounting pin connector, single row, 01x07, script generated (kicad-library-utils/schlib/autogen/connector/)"
"J7","Conn_01x05","","Connector_PinHeader_2.54mm:PinHeader_1x05_P2.54mm_Vertical","1","Generic connector, single row, 01x05, script generated (kicad-library-utils/schlib/autogen/connector/)"
"J10,J11","Conn_01x02_MountingPin","","Connector_JST:JST_GH_BM02B-GHS-TBT_1x02-1MP_P1.25mm_Vertical","2","Generic connectable mounting pin connector, single row, 01x02, script generated (kicad-library-utils/schlib/autogen/connector/)"
"L2","10uH 125mΩ 3.2A","","Inductor_SMD:L_Changjiang_FXL0530","1","Inductor"
"LED1,LED3,LED4","LED_0603_Amber","","PCM_LED_SMD_AKL:LED_0603_1608Metric","3","Amber SMD LED, 0603, Alternate KiCad Library"
"Q3,Q4,Q5,Q6,Q7,Q8","ISC030N10NM6","","ISC030N10NM6:IFX-PG-TDSON-8-36-V","6","Insulated-Gate Field-Effect Transistor (IGFET), N-Channel, Enhancement, Body Diode, Pin 1 Source, 2 Source, 3 Source, 4 Gate, 5 Drain, 6 Drain, 7 Drain, 8 Drain, 8 Pins"
"R10,R72","24.9k 1%","","Resistor_SMD:R_0402_1005Metric","2","Resistor"
"R11,R17,R18,R38,R40","10k 1%","","Resistor_SMD:R_0402_1005Metric","5","Resistor"
"R12,R16,R19","100k 1%","","Resistor_SMD:R_0402_1005Metric","3","Resistor"
"R13,R14,R15","56R 1%","","Resistor_SMD:R_0402_1005Metric","3","Resistor"
"R20,R21,R25,R26,R30,R31,R58","0R 1% 1/8W","","Resistor_SMD:R_0805_2012Metric,Resistor_SMD:R_0805_2012Metric_Pad1.20x1.40mm_HandSolder","7","Resistor"
"R22,R27,R32","3mΩ 3W 1%","","Resistor_SMD:R_2512_6332Metric_Pad1.40x3.35mm_HandSolder","3","Resistor"
"R36,R39,R42,R44","2k 1%","","Resistor_SMD:R_0402_1005Metric","4","Resistor"
"R37","10k NTC","https://www.murata.com/-/media/webrenewal/products/thermisto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","PCM_SparkFun-Resistor:R_0603_1608Metric","1","Temperature dependent resistor"
"R41,R62,R65,R66","1k 1%","","Resistor_SMD:R_0402_1005Metric","4","Resistor"
"R45,R46","60R4 1%","","Resistor_SMD:R_0805_2012Metric","2","Resistor"
"R47,R48,R49,R50,R51,R52,R53,R54","100R 1%","","Resistor_SMD:R_0402_1005Metric","8","Resistor"
"R73","12.4k 1%","","Resistor_SMD:R_0402_1005Metric","1","Resistor"
"SW1","SW_Push_DPDT","","PCM_SparkFun-Switch:Slide_DPDT_SMD_7.2x3.5mm","1","Momentary Switch, dual pole double throw"
"U1","AS5047P-ATSM","AS5047P-ATSM","TSSOP14_OSM","1",""
"U3","LMR36520ADDAR","https://www.ti.com/lit/gpn/lmr36520","DDA0008J","1",""
"U5","STM32G431RBTx","https://www.st.com/resource/en/datasheet/stm32g431rb.pdf","Package_QFP:LQFP-64_10x10mm_P0.5mm","1","STMicroelectronics Arm Cortex-M4 MCU, 128KB flash, 32KB RAM, 170 MHz, 1.71-3.6V, 52 GPIO, LQFP64"
"U6","DRV8323SRTAR","https://www.ti.com/lit/gpn/drv8323","RTA0040B","1",""
"U7","TLV75733PDRV","https://www.ti.com/lit/ds/symlink/tlv757p.pdf","PCM_SparkFun-Semiconductor-Standard:WDFN-6_2x2mm","1","1A Low IQ Small Size Low Dropout Voltage Regulator, Fixed Output 3.3V, WSON6"
"U8","TCAN1044AVDRQ1","https://www.ti.com/lit/gpn/tcan1044a-q1","D0008A-IPC_A","1",""
"X1","SMD3225-4","","PCM_Crystal_AKL:Crystal_SMD_3225-4Pin_3.2x2.5mm","1","SMD Quartz crystal, 4 terminals, 3.2mm x 2.5mm, Alternate KiCad Library"

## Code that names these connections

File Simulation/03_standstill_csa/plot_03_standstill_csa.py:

"""Reproduces results/fig03_standstill_csa.png from 03_standstill_csa.raw.
Run 03_standstill_csa.asc in LTspice first (same folder), then:  python3 plot_03_standstill_csa.py   (needs numpy + matplotlib)
Single run (no .step). Shows the last two PWM periods; dashed lines = ADC sample instants (carrier peak).
"""
import os, sys
import numpy as np
import matplotlib
matplotlib.use('Agg')
import matplotlib.pyplot as plt

HERE = os.path.dirname(os.path.abspath(__file__))
sys.path.insert(0, os.path.join(HERE, '..', 'common'))
from ltspice_raw import read_raw

plt.rcParams.update({'font.size': 8, 'axes.grid': True, 'grid.alpha': 0.3, 'figure.dpi': 130})
s = read_raw(os.path.join(HERE, '03_standstill_csa.raw'))[0]
OUT = os.path.join(HERE, 'results', 'fig03_standstill_csa.png')
fsw, G, Rsh, VREF = 25e3, 20, 3e-3, 3.3
t = s['time']
m = t > 23 / fsw
tu = t[m] * 1e6
samples = [23.5 / fsw * 1e6, 24.5 / fsw * 1e6]

fig, ax = plt.subplots(3, 1, figsize=(7, 6.4), sharex=True)
ax[0].plot(tu, s['i(la)'][m], label='I phase A (true)')
ax[0].plot(tu, s['i(lb)'][m], label='I phase B (true)')
ax[0].set_ylabel('A'); ax[0].legend(fontsize=7)
ax[0].set_title('Fig 03 - 5 A hold along +alpha at 30 V: ripple and what the CSA shows')
ax[1].plot(tu, s['v(soa)'][m], label='SOA (DRV8323 pin, TP20)')
ax[1].plot(tu, s['v(filter_soa)'][m], label='FILTER_SOA (MCU ADC, TP17)')
ax[1].plot(tu, VREF / 2 + G * Rsh * s['i(la)'][m], 'k:', lw=1, label='VREF/2 + G*Rsh*I_A (ideal)')
ax[1].set_ylabel('V'); ax[1].legend(fontsize=7)
ax[2].plot(tu, s['v(sw_a)'][m], label='SW_A')
ax[2].plot(tu, s['v(inla)'][m] * 10, label='PWM_PHASEA_L x10 (TP22, scope trigger)')
ax[2].set_ylabel('V'); ax[2].set_xlabel('time (us)'); ax[2].legend(fontsize=7)
for a in ax:
    for x in samples:
        a.axvline(x, color='r', ls='--', lw=0.8)
ax[1].text(samples[0] + 0.5, ax[1].get_ylim()[0] + 0.02, 'ADC sample', color='r', fontsize=7)
fig.tight_layout(); fig.savefig(OUT); print('wrote', OUT)
